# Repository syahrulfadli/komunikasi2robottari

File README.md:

# Komunikasi 2 Robot untuk Kontes Tari
Sketch Program Komunikasi Robot Tari dengan 3 Module Bluetooth.

Modul bluetooth yang digunakan ada 4. Satu pada masing-masing robot dan dua untuk rangkaian pendeteksi musik.

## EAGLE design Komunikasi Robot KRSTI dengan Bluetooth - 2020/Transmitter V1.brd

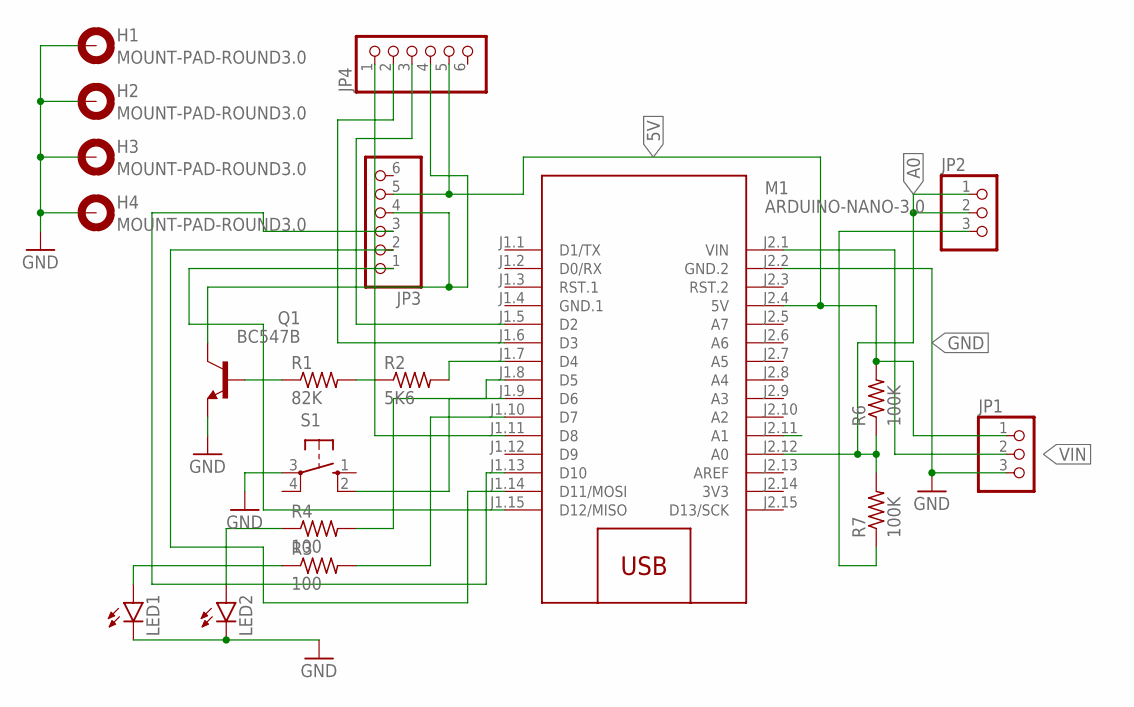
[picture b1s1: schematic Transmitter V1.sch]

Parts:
H1, H2, H3, H4: MOUNT-PAD-ROUND3.0; 3,0-PAD
JP1, JP2: PINHD-1X3; 1X03
JP3, JP4: PINHD-1X6; 1X06
LED1, LED2: LED3MM
M1: ARDUINO-NANO-3.0
Q1: BC547B; TO92
R1: 82K; 0207/7
R2: 5K6; 0207/7
R3, R4: 100; 0207/7
R6, R7: 100K; 0207/7
S1: 10-XX; B3F-10XX

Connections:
3V3: M1.J2.14 (3V3)
5V: JP1.1, JP3.5, JP4.5, M1.J2.4 (5V), R6.2
A0: JP2.1, JP2.2, M1.J2.12 (A0), R6.1, R7.2
GND: H1.B3,0, H2.B3,0, H3.B3,0, H4.B3,0, JP1.3, LED1.K (C), LED2.K (C), M1.J2.2 (GND.2), Q1.1 (E), S1.3
GND.1: M1.J1.4 (GND.1)
unnamed: M1.J1.7 (D4), R2.2
unnamed: Q1.2 (B), R1.1
unnamed: R1.2, R2.1
unnamed: JP3.4, JP4.4, Q1.3 (C)
unnamed: M1.J1.8 (D5), S1.2 (S1)
unnamed: JP3.2, M1.J1.14 (D11/MOSI)
unnamed: LED2.A, R4.1
unnamed: LED1.A, R3.1
unnamed: M1.J1.10 (D7), R3.2
unnamed: M1.J1.9 (D6), R4.2
unnamed: JP4.2, M1.J1.6 (D3)
unnamed: JP2.3, R7.1
unnamed: JP4.3, M1.J1.5 (D2)
unnamed: JP3.3, M1.J1.13 (D10)
unnamed: JP3.1, M1.J1.15 (D12/MISO)
unnamed: JP4.1, M1.J1.11 (D8)
VIN: JP1.2, M1.J2.1 (VIN)

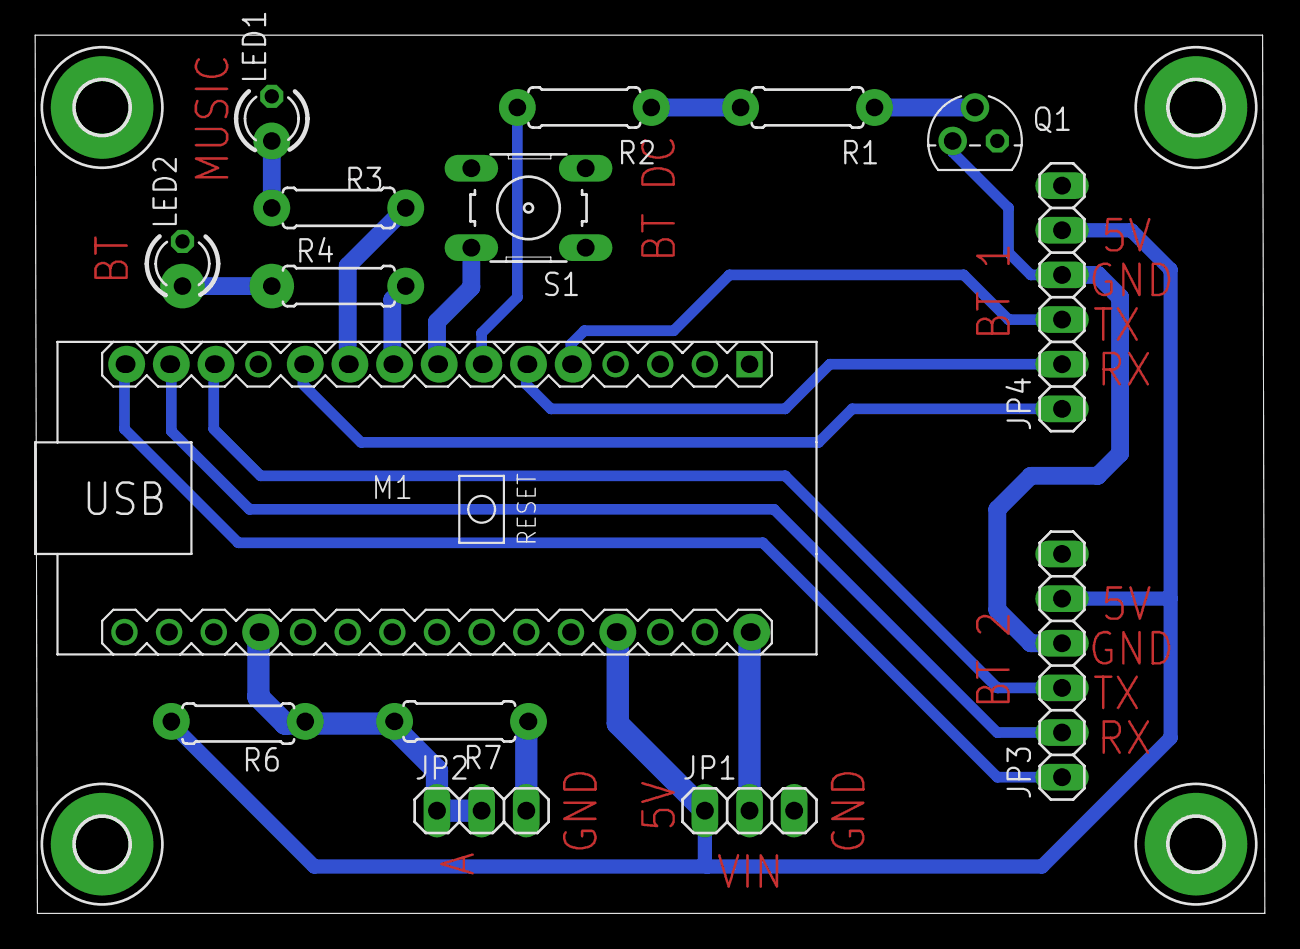
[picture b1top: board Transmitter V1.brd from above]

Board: 2 copper layers, 70.0 x 50.0 mm, 19 parts (0 on the bottom side), 20 nets.

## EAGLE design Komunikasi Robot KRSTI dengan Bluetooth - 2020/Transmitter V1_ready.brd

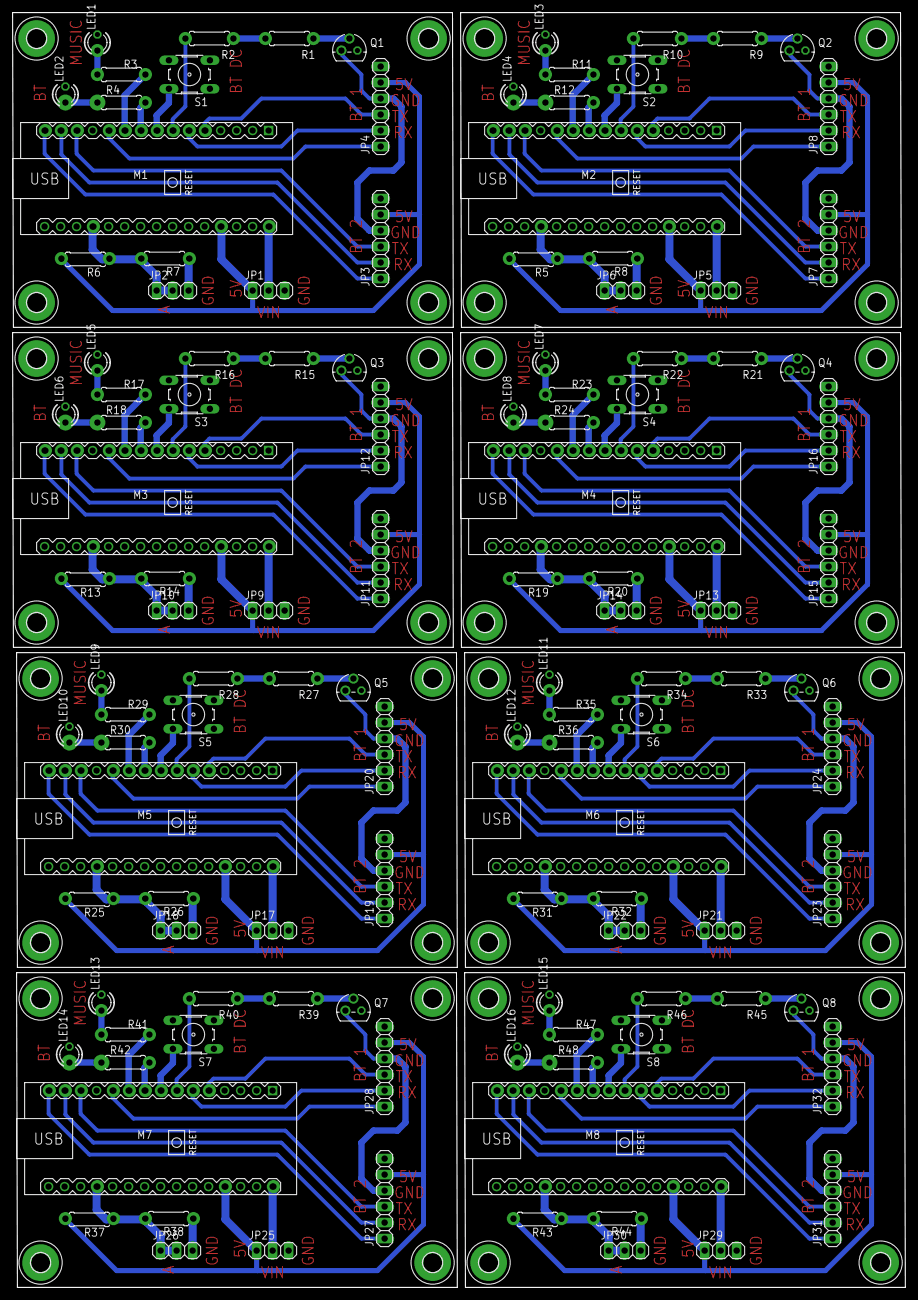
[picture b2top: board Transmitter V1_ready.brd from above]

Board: 2 copper layers, 141.7 x 202.4 mm, 152 parts (0 on the bottom side), 160 nets.

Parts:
H1, H2, H3, H4, H5, H6, H7, H8, H9, H10, H11, H12, H13, H14, H15, H16, H17, H18, H19, H20, H21, H22, H23, H24, H25, H26, H27, H28, H29, H30, H31, H32: MOUNT-PAD-ROUND3.0; 3,0-PAD
JP1, JP2, JP5, JP6, JP9, JP10, JP13, JP14, JP17, JP18, JP21, JP22, JP25, JP26, JP29, JP30: 1X03
JP3, JP4, JP7, JP8, JP11, JP12, JP15, JP16, JP19, JP20, JP23, JP24, JP27, JP28, JP31, JP32: 1X06
LED1, LED2, LED3, LED4, LED5, LED6, LED7, LED8, LED9, LED10, LED11, LED12, LED13, LED14, LED15, LED16: LED3MM
M1, M2, M3, M4, M5, M6, M7, M8: ARDUINO-NANO-3.0
Q1, Q2, Q3, Q4, Q5, Q6, Q7, Q8: BC547B; TO92
R1, R9, R15, R21, R27, R33, R39, R45: 82K; 0207/7
R2, R10, R16, R22, R28, R34, R40, R46: 5K6; 0207/7
R3, R4, R11, R12, R17, R18, R23, R24, R29, R30, R35, R36, R41, R42, R47, R48: 100; 0207/7
R5, R6, R7, R8, R13, R14, R19, R20, R25, R26, R31, R32, R37, R38, R43, R44: 100K; 0207/7
S1, S2, S3, S4, S5, S6, S7, S8: B3F-10XX

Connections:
5V: JP1.1, JP3.5, JP4.5, M1.J2.4, R6.2
5V1: JP5.1, JP7.5, JP8.5, M2.J2.4, R5.2
5V2: JP9.1, JP11.5, JP12.5, M3.J2.4, R13.2
5V3: JP13.1, JP15.5, JP16.5, M4.J2.4, R19.2
5V4: JP17.1, JP19.5, JP20.5, M5.J2.4, R25.2
5V5: JP21.1, JP23.5, JP24.5, M6.J2.4, R31.2
5V6: JP25.1, JP27.5, JP28.5, M7.J2.4, R37.2
5V7: JP29.1, JP31.5, JP32.5, M8.J2.4, R43.2
A0: JP2.1, JP2.2, M1.J2.12, R6.1, R7.2
A1: JP6.1, JP6.2, M2.J2.12, R5.1, R8.2
A2: JP10.1, JP10.2, M3.J2.12, R13.1, R14.2
A3: JP14.1, JP14.2, M4.J2.12, R19.1, R20.2
A4: JP18.1, JP18.2, M5.J2.12, R25.1, R26.2
A5: JP22.1, JP22.2, M6.J2.12, R31.1, R32.2
A6: JP26.1, JP26.2, M7.J2.12, R37.1, R38.2
A7: JP30.1, JP30.2, M8.J2.12, R43.1, R44.2
GND: H1.B3,0, H2.B3,0, H3.B3,0, H4.B3,0, JP1.3, LED1.K, LED2.K, M1.J2.2, Q1.1, S1.3
GND1: H5.B3,0, H6.B3,0, H7.B3,0, H8.B3,0, JP5.3, LED3.K, LED4.K, M2.J2.2, Q2.1, S2.3
GND2: H9.B3,0, H10.B3,0, H11.B3,0, H12.B3,0, JP9.3, LED5.K, LED6.K, M3.J2.2, Q3.1, S3.3
GND3: H13.B3,0, H14.B3,0, H15.B3,0, H16.B3,0, JP13.3, LED7.K, LED8.K, M4.J2.2, Q4.1, S4.3
GND4: H17.B3,0, H18.B3,0, H19.B3,0, H20.B3,0, JP17.3, LED9.K, LED10.K, M5.J2.2, Q5.1, S5.3
GND5: H21.B3,0, H22.B3,0, H23.B3,0, H24.B3,0, JP21.3, LED11.K, LED12.K, M6.J2.2, Q6.1, S6.3
GND6: H25.B3,0, H26.B3,0, H27.B3,0, H28.B3,0, JP25.3, LED13.K, LED14.K, M7.J2.2, Q7.1, S7.3
GND7: H29.B3,0, H30.B3,0, H31.B3,0, H32.B3,0, JP29.3, LED15.K, LED16.K, M8.J2.2, Q8.1, S8.3
unnamed: M1.J1.7, R2.2
unnamed: Q1.2, R1.1
unnamed: R1.2, R2.1
unnamed: JP3.4, JP4.4, Q1.3
unnamed: M1.J1.8, S1.2
unnamed: JP3.2, M1.J1.14
unnamed: LED2.A, R4.1
unnamed: LED1.A, R3.1
unnamed: M1.J1.10, R3.2
unnamed: M1.J1.9, R4.2
unnamed: JP4.2, M1.J1.6
unnamed: JP2.3, R7.1
unnamed: JP4.3, M1.J1.5
unnamed: JP3.3, M1.J1.13
unnamed: JP3.1, M1.J1.15
unnamed: JP6.3, R8.1
unnamed: JP8.3, M2.J1.5
unnamed: JP4.1, M1.J1.11
unnamed: JP8.2, M2.J1.6
unnamed: M2.J1.7, R10.2
unnamed: Q2.2, R9.1
unnamed: R9.2, R10.1
unnamed: JP7.4, JP8.4, Q2.3
unnamed: M2.J1.8, S2.2
unnamed: LED4.A, R12.1
unnamed: LED3.A, R11.1
unnamed: M2.J1.10, R11.2
unnamed: M2.J1.9, R12.2
unnamed: JP7.2, M2.J1.14
unnamed: JP7.3, M2.J1.13
unnamed: JP7.1, M2.J1.15
unnamed: JP8.1, M2.J1.11
unnamed: JP10.3, R14.1
unnamed: JP12.3, M3.J1.5
unnamed: JP12.2, M3.J1.6
unnamed: M3.J1.7, R16.2
unnamed: Q3.2, R15.1
unnamed: R15.2, R16.1
unnamed: JP11.4, JP12.4, Q3.3
unnamed: M3.J1.8, S3.2
unnamed: LED6.A, R18.1
unnamed: LED5.A, R17.1
unnamed: M3.J1.10, R17.2
unnamed: M3.J1.9, R18.2
unnamed: JP11.2, M3.J1.14
unnamed: JP11.3, M3.J1.13
unnamed: JP11.1, M3.J1.15
unnamed: JP12.1, M3.J1.11
unnamed: JP14.3, R20.1
unnamed: JP16.3, M4.J1.5
unnamed: JP16.2, M4.J1.6
unnamed: M4.J1.7, R22.2
unnamed: Q4.2, R21.1
unnamed: R21.2, R22.1
unnamed: JP15.4, JP16.4, Q4.3
unnamed: M4.J1.8, S4.2
unnamed: LED8.A, R24.1
unnamed: LED7.A, R23.1
unnamed: M4.J1.10, R23.2
unnamed: M4.J1.9, R24.2
unnamed: JP15.2, M4.J1.14
unnamed: JP15.3, M4.J1.13
unnamed: JP15.1, M4.J1.15
unnamed: JP16.1, M4.J1.11
unnamed: JP18.3, R26.1
unnamed: JP20.3, M5.J1.5
unnamed: JP20.2, M5.J1.6
unnamed: M5.J1.7, R28.2
unnamed: Q5.2, R27.1
unnamed: R27.2, R28.1
unnamed: JP19.4, JP20.4, Q5.3
unnamed: M5.J1.8, S5.2
unnamed: LED10.A, R30.1
unnamed: LED9.A, R29.1
unnamed: M5.J1.10, R29.2
unnamed: M5.J1.9, R30.2
unnamed: JP19.2, M5.J1.14
unnamed: JP19.3, M5.J1.13
unnamed: JP19.1, M5.J1.15
unnamed: JP20.1, M5.J1.11
unnamed: JP22.3, R32.1
unnamed: JP24.3, M6.J1.5
unnamed: JP24.2, M6.J1.6
unnamed: M6.J1.7, R34.2
unnamed: Q6.2, R33.1
unnamed: R33.2, R34.1
unnamed: JP23.4, JP24.4, Q6.3
unnamed: M6.J1.8, S6.2
unnamed: LED12.A, R36.1
unnamed: LED11.A, R35.1
unnamed: M6.J1.10, R35.2
unnamed: M6.J1.9, R36.2
unnamed: JP23.2, M6.J1.14
unnamed: JP23.3, M6.J1.13
unnamed: JP23.1, M6.J1.15
unnamed: JP24.1, M6.J1.11
unnamed: JP26.3, R38.1
unnamed: JP28.3, M7.J1.5
unnamed: JP28.2, M7.J1.6
unnamed: M7.J1.7, R40.2
unnamed: Q7.2, R39.1
unnamed: R39.2, R40.1
unnamed: JP27.4, JP28.4, Q7.3
unnamed: M7.J1.8, S7.2
unnamed: LED14.A, R42.1
unnamed: LED13.A, R41.1
unnamed: M7.J1.10, R41.2
unnamed: M7.J1.9, R42.2
unnamed: JP27.2, M7.J1.14
unnamed: JP27.3, M7.J1.13
unnamed: JP27.1, M7.J1.15
unnamed: JP28.1, M7.J1.11
unnamed: JP30.3, R44.1
unnamed: JP32.3, M8.J1.5
unnamed: JP32.2, M8.J1.6
unnamed: M8.J1.7, R46.2
unnamed: Q8.2, R45.1
unnamed: R45.2, R46.1
unnamed: JP31.4, JP32.4, Q8.3
unnamed: M8.J1.8, S8.2
unnamed: LED16.A, R48.1
unnamed: LED15.A, R47.1
unnamed: M8.J1.10, R47.2
unnamed: M8.J1.9, R48.2
unnamed: JP31.2, M8.J1.14
unnamed: JP31.3, M8.J1.13
unnamed: JP31.1, M8.J1.15
unnamed: JP32.1, M8.J1.11
VIN: JP1.2, M1.J2.1
VIN1: JP5.2, M2.J2.1
VIN2: JP9.2, M3.J2.1
VIN3: JP13.2, M4.J2.1
VIN4: JP17.2, M5.J2.1
VIN5: JP21.2, M6.J2.1
VIN6: JP25.2, M7.J2.1
VIN7: JP29.2, M8.J2.1

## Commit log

2020-09-18 program tes tari

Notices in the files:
parts and their libraries:
diy-modules: Released under the Creative Commons Attribution 4.0 International License: http://creativecommons.org/licenses/by/4.0
